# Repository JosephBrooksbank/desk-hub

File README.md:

# desk-hub
A custom KM/USB switch for my desk. 

## Goals
- 10(+) USB Ports
- 2 input switchable
- Stable 5V power to all ports
- Separate overdraw protection
- Electronically controllable
- Visual indicator of port use and overdraw
- Multiple switching points to split input across machines
- USB3?

## Rationale 
Currently, I have two UGreen 4 port USB switches taped to my desk. Each morning I press the button on each to switch to work, and each afternoon I press the button to switch back. They cannot always reliably provide enough amps to each downstream port and my audio cuts out sometimes. Very occasionally they initialize incorrectly and I must remove all connections and reconnect them to gain control again. The downstream and upstream ports are also all on opposite sides, leading to many wires curling back on themselves. 

I aim to solve these issues in an overengineered board of my own design, as an opportunity to learn slightly higher speed PCB design and 4 layer boards.

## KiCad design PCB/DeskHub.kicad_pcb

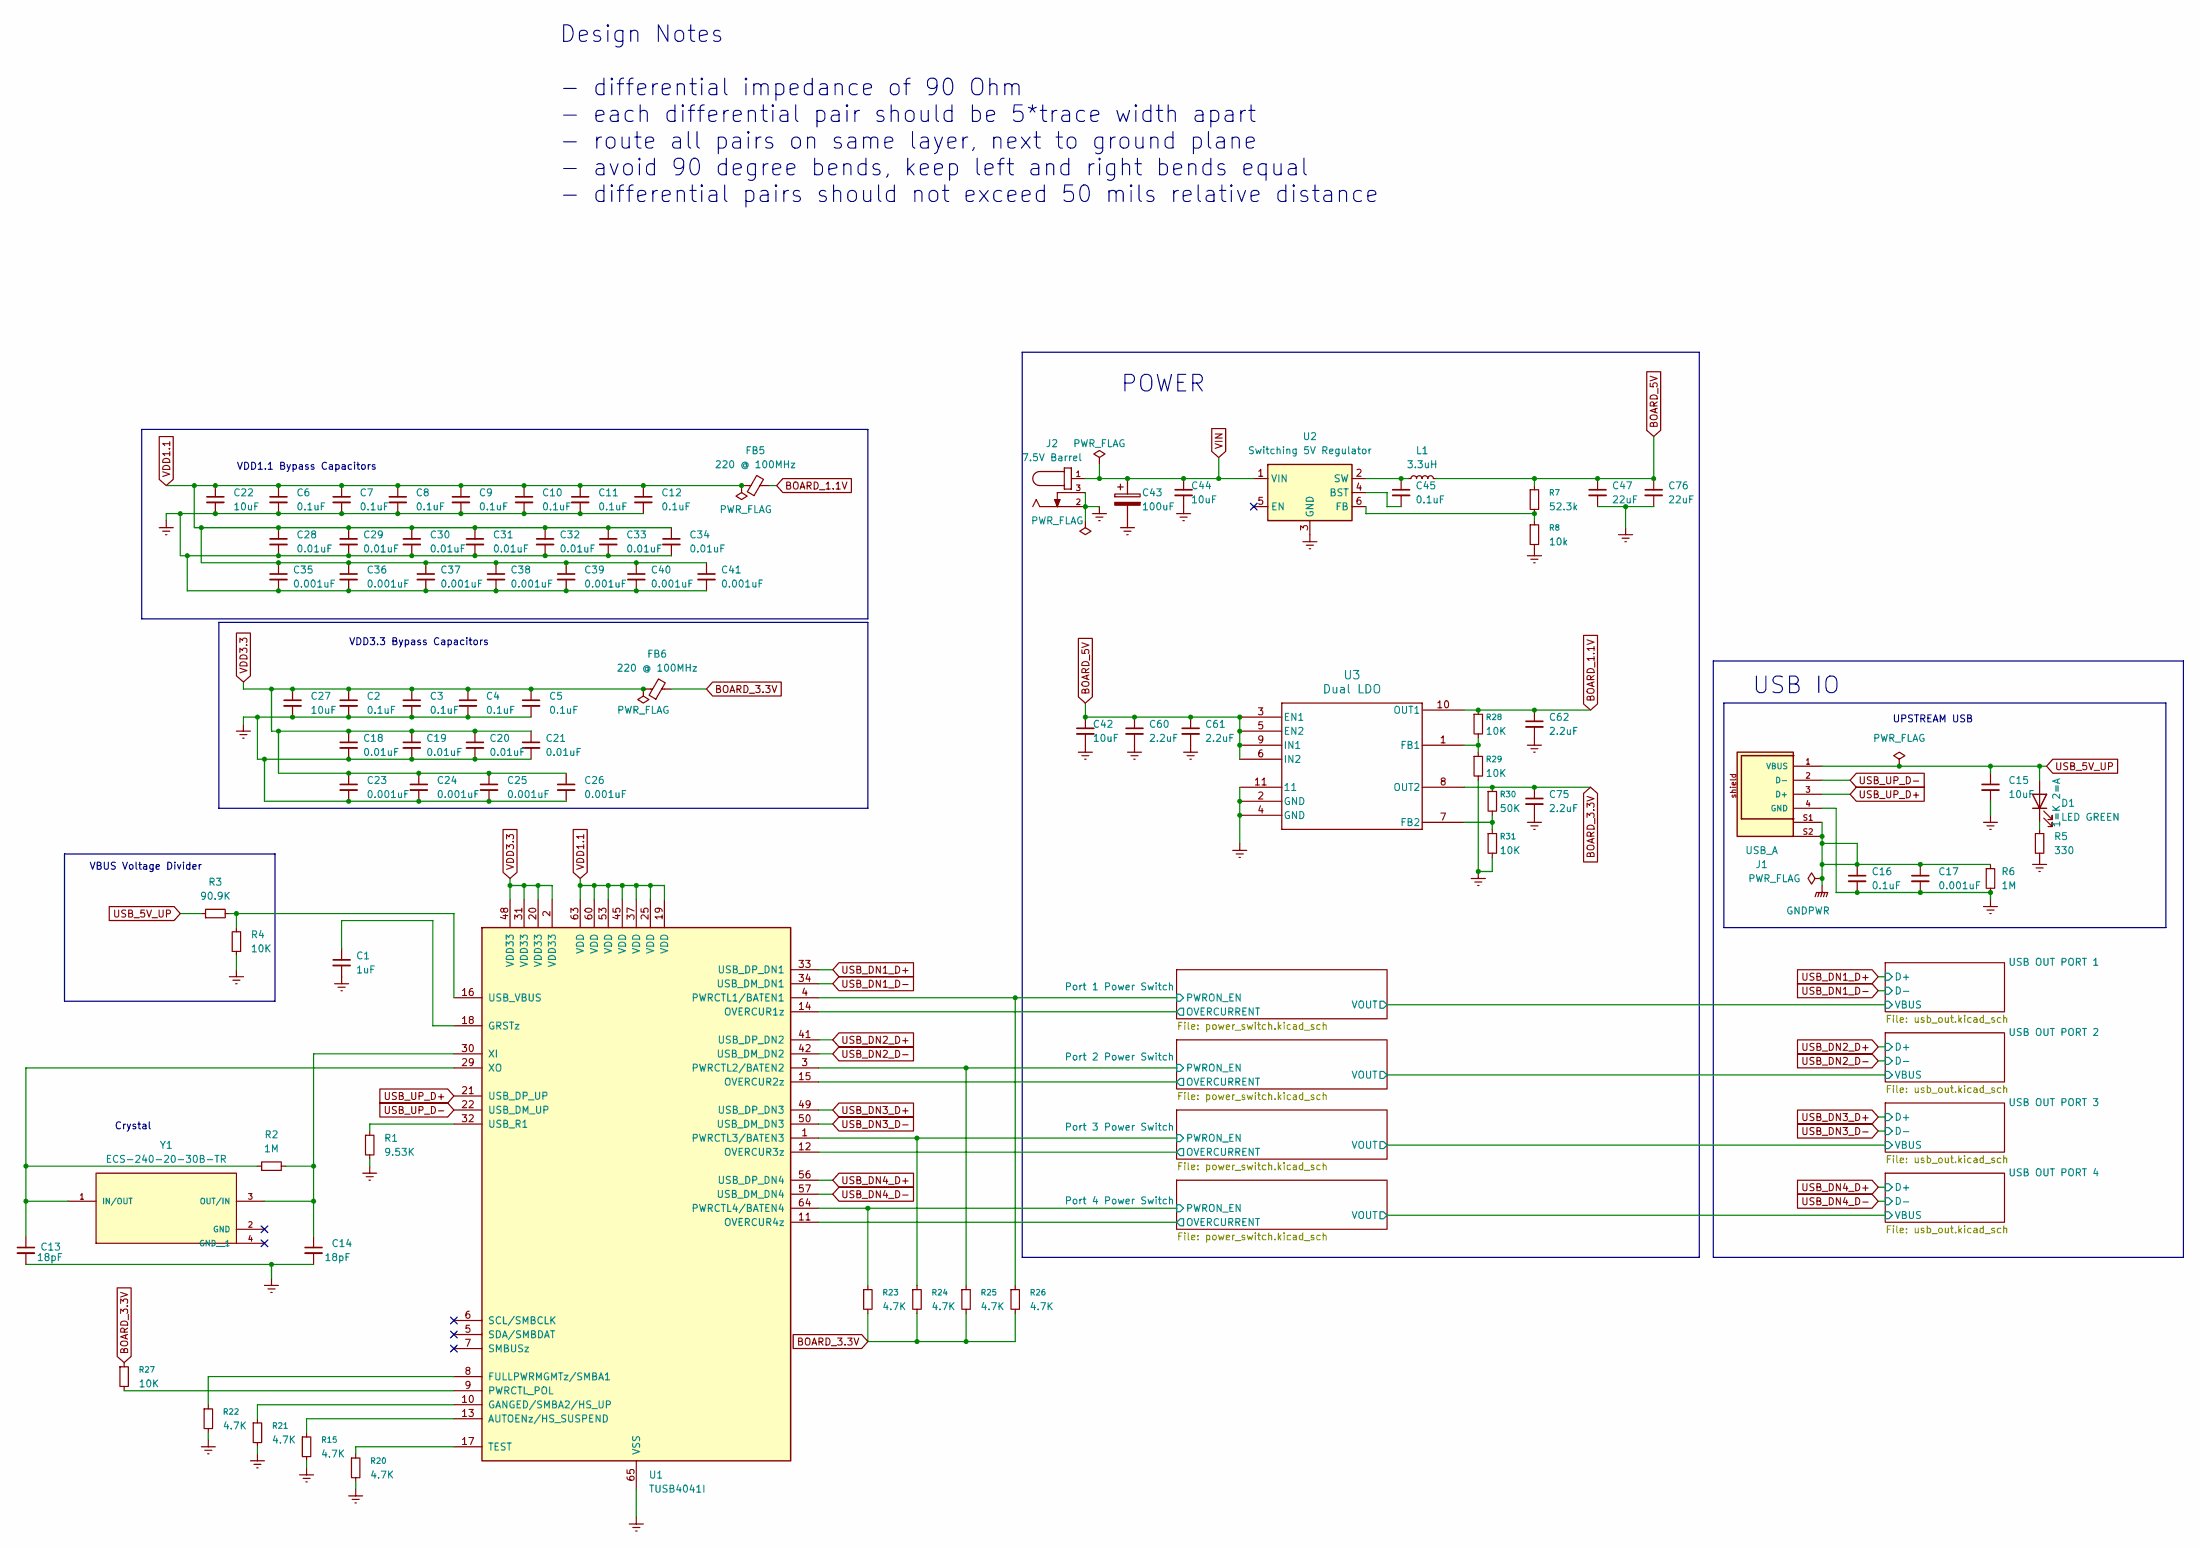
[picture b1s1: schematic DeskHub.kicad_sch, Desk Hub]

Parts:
C1: 1uF; C_0402_1005Metric
C2, C3, C4, C5, C6, C7, C8, C9, C10, C11, C12: 0.1uF; C_0201_0603Metric
C13, C14: 18pF; C_0402_1005Metric
C15, C22, C27, C42, C44: 10uF; C_1206_3216Metric
C16, C45: 0.1uF; C_0402_1005Metric
C17: 0.001uF; C_0402_1005Metric
C18, C19, C20, C21, C28, C29, C30, C31, C32, C33, C34: 0.01uF; C_0201_0603Metric
C23, C24, C25, C26, C35, C36, C37, C38, C39, C40, C41: 0.001uF; C_0201_0603Metric
C43: 100uF; CP_Elec_6.3x7.7
C47, C76: 22uF; C_0201_0603Metric
C60, C61, C62, C75: 2.2uF; C_0805_2012Metric
D1: LED GREEN; LED_0603_1608Metric
FB5, FB6: 220 @ 100MHz; BEADC1608X95N
J1: USB_A; 61400416021
J2: 7.5V Barrel; 694108301002
L1: 3.3uH; NRS5030T3R3MMGJ
R1: 9.53K; R_0402_1005Metric
R2, R6: 1M; R_0402_1005Metric
R3: 90.9K; R_0402_1005Metric
R4, R27, R28, R29, R31: 10K; R_0402_1005Metric
R5: 330; R_0402_1005Metric
R7: 52.3k; R_0402_1005Metric
R8: 10k; R_0402_1005Metric
R15, R20, R21, R22, R23, R24, R25, R26: 4.7K; R_0402_1005Metric
R30: 50K; R_0402_1005Metric
U1: TUSB4041I; HTQFP-64-1EP_10x10mm_P0.5mm_EP8x8mm_Mask4.4x4.4mm_ThermalVi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
U2: Switching 5V Regulator; SOT-563
U3: Dual LDO; SON_1PDSQR_TEX
Y1: ECS-240-20-30B-TR; XTAL_ECS-240-20-30B-TR

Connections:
/Port 1 Power Switch/OVERCURRENT: U1.14 (OVERCUR1z); also elsewhere on the board
/Port 1 Power Switch/PWRON_EN: R26.1, U1.4 (PWRCTL1/BATEN1); also elsewhere on the board
/Port 2 Power Switch/OVERCURRENT: U1.15 (OVERCUR2z); also elsewhere on the board
/Port 2 Power Switch/PWRON_EN: R25.1, U1.3 (PWRCTL2/BATEN2); also elsewhere on the board
/Port 3 Power Switch/OVERCURRENT: U1.12 (OVERCUR3z); also elsewhere on the board
/Port 3 Power Switch/PWRON_EN: R24.1, U1.1 (PWRCTL3/BATEN3); also elsewhere on the board
/Port 4 Power Switch/OVERCURRENT: U1.11 (OVERCUR4z); also elsewhere on the board
/Port 4 Power Switch/PWRON_EN: R23.1, U1.64 (PWRCTL4/BATEN4); also elsewhere on the board
BOARD_1.1V: C62.1, FB5.2, R28.1, U3.10 (OUT1)
BOARD_3.3V: C75.1, FB6.2, R23.2, R24.2, R25.2, R26.2, R27.1, R30.1, U3.8 (OUT2); also elsewhere on the board
BOARD_5V: C42.1, C47.1, C60.1, C61.1, C76.1, L1.2, R7.1, U3.3 (EN1), U3.5 (EN2), U3.6 (IN2), U3.9 (IN1); also elsewhere on the board
Earth: C1.2, C2.2, C3.2, C4.2, C5.2, C6.2, C7.2, C8.2, C9.2, C10.2, C11.2, C12.2, C13.2, C14.2, C15.2, C16.2, C17.2, C18.2, C19.2, C20.2, C21.2, C22.2, C23.2, C24.2, C25.2, C26.2, C27.2, C28.2, C29.2, C30.2, C31.2, C32.2, C33.2, C34.2, C35.2, C36.2, C37.2, C38.2, C39.2, C40.2, C41.2, C42.2, C43.2, C44.2, C47.2, C60.2, C61.2, C62.2, C75.2, C76.2, J1.4 (GND), J2.2, J2.3, R1.2, R4.1, R5.2, R6.2, R8.2, R15.2, R20.2, R21.2, R22.2, R29.2, R31.2, U1.65 (VSS), U2.3 (GND), U3.2 (GND), U3.4 (GND), U3.11; also elsewhere on the board
GNDPWR: C16.1, C17.1, J1.S1, J1.S2, R6.1; also elsewhere on the board
unnamed: D1.1 (K), R5.1
unnamed: R15.1, U1.13 (AUTOENz/HS_SUSPEND)
unnamed: R22.1, U1.8 (FULLPWRMGMTz/SMBA1)
unnamed: R21.1, U1.10 (GANGED/SMBA2/HS_UP)
unnamed: C1.1, U1.18 (GRSTz)
unnamed: R27.2, U1.9 (PWRCTL_POL)
unnamed: R20.1, U1.17 (TEST)
unnamed: R1.1, U1.32 (USB_R1)
unnamed: R3.2, R4.2, U1.16 (USB_VBUS)
unnamed: C14.1, R2.2, U1.30 (XI), Y1.3 (OUT/IN)
unnamed: C13.1, R2.1, U1.29 (XO), Y1.1 (IN/OUT)
unnamed: C45.2, U2.4 (BST)
unnamed: R7.2, R8.1, U2.6 (FB)
unnamed: C45.1, L1.1, U2.2 (SW)
unnamed: R28.2, R29.1, U3.1 (FB1)
unnamed: R30.2, R31.1, U3.7 (FB2)
USB_5V_UP: C15.1, D1.2 (A), J1.1 (VBUS), R3.1
USB_DN1_D+: U1.33 (USB_DP_DN1); also elsewhere on the board
USB_DN1_D-: U1.34 (USB_DM_DN1); also elsewhere on the board
USB_DN2_D+: U1.41 (USB_DP_DN2); also elsewhere on the board
USB_DN2_D-: U1.42 (USB_DM_DN2); also elsewhere on the board
USB_DN3_D+: U1.49 (USB_DP_DN3); also elsewhere on the board
USB_DN3_D-: U1.50 (USB_DM_DN3); also elsewhere on the board
USB_DN4_D+: U1.56 (USB_DP_DN4); also elsewhere on the board
USB_DN4_D-: U1.57 (USB_DM_DN4); also elsewhere on the board
USB_UP_D+: J1.3 (D+), U1.21 (USB_DP_UP)
USB_UP_D-: J1.2 (D-), U1.22 (USB_DM_UP)
VDD1.1: C6.1, C7.1, C8.1, C9.1, C10.1, C11.1, C12.1, C22.1, C28.1, C29.1, C30.1, C31.1, C32.1, C33.1, C34.1, C35.1, C36.1, C37.1, C38.1, C39.1, C40.1, C41.1, FB5.1, U1.19 (VDD), U1.25 (VDD), U1.37 (VDD), U1.45 (VDD), U1.53 (VDD), U1.60 (VDD), U1.63 (VDD)
VDD3.3: C2.1, C3.1, C4.1, C5.1, C18.1, C19.1, C20.1, C21.1, C23.1, C24.1, C25.1, C26.1, C27.1, FB6.1, U1.2 (VDD33), U1.20 (VDD33), U1.31 (VDD33), U1.48 (VDD33)
VIN: C43.1, C44.1, J2.1, U2.1 (VIN)

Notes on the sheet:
UPSTREAM USB
VDD1.1 Bypass Capacitors
Design Notes - differential impedance of 90 Ohm - each differential pair should be 5*trace width apart - route all pairs on same layer, next to ground plane - avoid 90 degree bends, keep left and right bends equal - differential pairs should not exceed 50 mils relative distance
VDD3.3 Bypass Capacitors
USB IO
Crystal
POWER
VBUS Voltage Divider

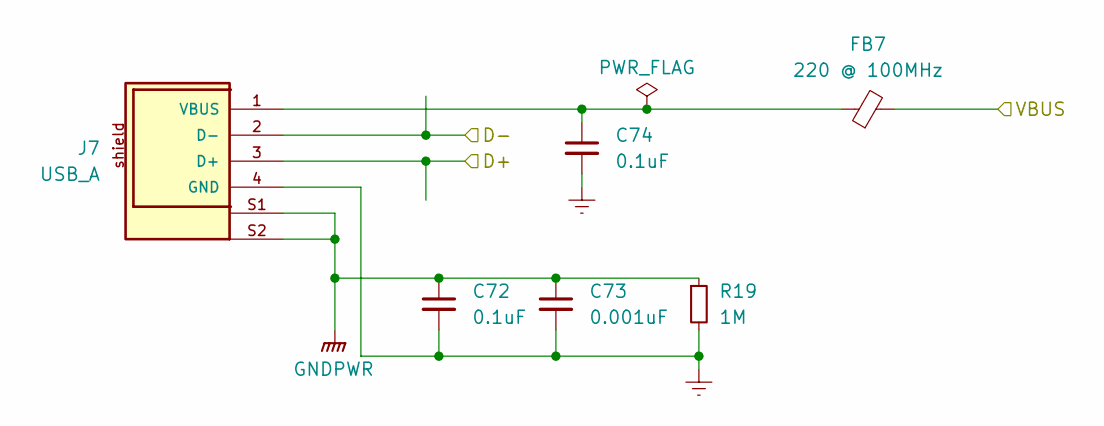
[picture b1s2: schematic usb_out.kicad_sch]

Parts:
C72, C74: 0.1uF; C_0402_1005Metric
C73: 0.001uF; C_0402_1005Metric
FB7: 220 @ 100MHz; BEADC1608X95N
J7: USB_A; 61400416021
R19: 1M; R_0402_1005Metric

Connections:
/Port 1 Power Switch/VOUT: FB7.2; also elsewhere on the board
Earth: C72.2, C73.2, C74.2, J7.4 (GND), R19.2; also elsewhere on the board
GNDPWR: C72.1, C73.1, J7.S1, J7.S2, R19.1; also elsewhere on the board
unnamed: C74.1, FB7.1, J7.1 (VBUS)
USB_DN1_D+: J7.3 (D+); also elsewhere on the board
USB_DN1_D-: J7.2 (D-); also elsewhere on the board

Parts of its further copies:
C63, C65, C66, C68, C69, C71: 0.1uF; C_0402_1005Metric
C64, C67, C70: 0.001uF; C_0402_1005Metric
FB2, FB3, FB4: 220 @ 100MHz; BEADC1608X95N
J4, J5, J6: USB_A; 61400416021
R16, R17, R18: 1M; R_0402_1005Metric

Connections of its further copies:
/Port 2 Power Switch/VOUT: FB2.2; also elsewhere on the board
/Port 3 Power Switch/VOUT: FB3.2; also elsewhere on the board
/Port 4 Power Switch/VOUT: FB4.2; also elsewhere on the board
Earth: C63.2, C64.2, C65.2, C66.2, C67.2, C68.2, C69.2, C70.2, C71.2, J4.4 (GND), J5.4 (GND), J6.4 (GND), R16.2, R17.2, R18.2; also elsewhere on the board
GNDPWR: C63.1, C64.1, C66.1, C67.1, C69.1, C70.1, J4.S1, J4.S2, J5.S1, J5.S2, J6.S1, J6.S2, R16.1, R17.1, R18.1; also elsewhere on the board
unnamed: C65.1, FB2.1, J4.1 (VBUS)
unnamed: C68.1, FB3.1, J5.1 (VBUS)
unnamed: C71.1, FB4.1, J6.1 (VBUS)
USB_DN2_D+: J4.3 (D+); also elsewhere on the board
USB_DN2_D-: J4.2 (D-); also elsewhere on the board
USB_DN3_D+: J5.3 (D+); also elsewhere on the board
USB_DN3_D-: J5.2 (D-); also elsewhere on the board
USB_DN4_D+: J6.3 (D+); also elsewhere on the board
USB_DN4_D-: J6.2 (D-); also elsewhere on the board

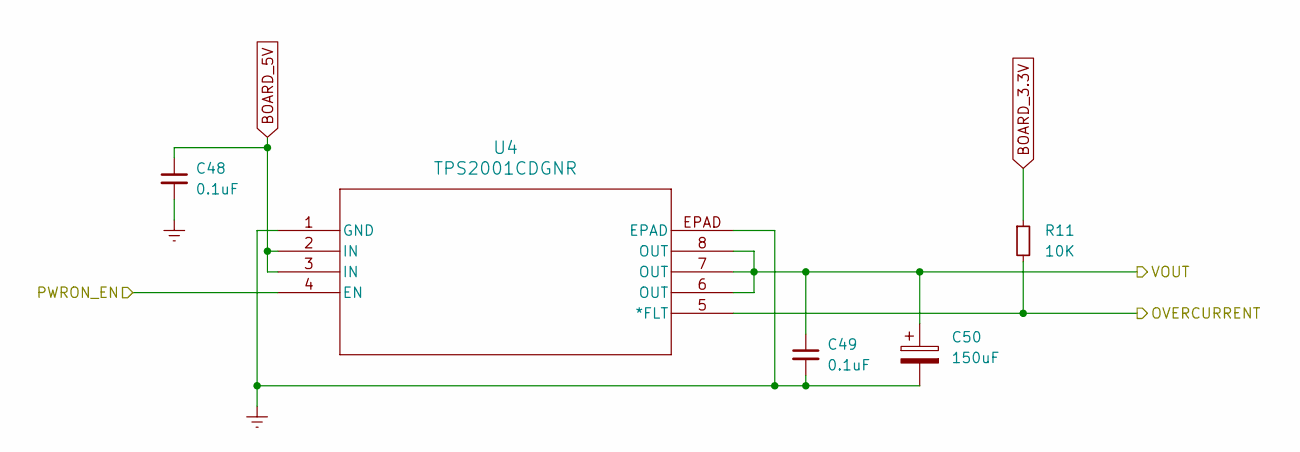
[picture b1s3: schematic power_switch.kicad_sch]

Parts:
C48, C49: 0.1uF; C_0402_1005Metric
C50: 150uF; CAP_EEFCX0J151XR
R11: 10K; R_0402_1005Metric
U4: TPS2001CDGNR; DGN8_1P89X1P57

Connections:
/Port 1 Power Switch/OVERCURRENT: R11.2, U4.5 (*FLT); also elsewhere on the board
/Port 1 Power Switch/PWRON_EN: U4.4 (EN); also elsewhere on the board
/Port 1 Power Switch/VOUT: C49.1, C50.1, U4.6 (OUT), U4.7 (OUT), U4.8 (OUT); also elsewhere on the board
BOARD_3.3V: R11.1; also elsewhere on the board
BOARD_5V: C48.1, U4.2 (IN), U4.3 (IN); also elsewhere on the board
Earth: C48.2, C49.2, C50.2, U4.1 (GND), U4.EPAD; also elsewhere on the board

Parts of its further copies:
C51, C52, C54, C55, C57, C58: 0.1uF; C_0402_1005Metric
C53, C56, C59: 150uF; CAP_EEFCX0J151XR
R12, R13, R14: 10K; R_0402_1005Metric
U5, U6, U7: TPS2001CDGNR; DGN8_1P89X1P57

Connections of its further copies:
/Port 2 Power Switch/OVERCURRENT: R12.2, U5.5 (*FLT); also elsewhere on the board
/Port 2 Power Switch/PWRON_EN: U5.4 (EN); also elsewhere on the board
/Port 2 Power Switch/VOUT: C52.1, C53.1, U5.6 (OUT), U5.7 (OUT), U5.8 (OUT); also elsewhere on the board
/Port 3 Power Switch/OVERCURRENT: R13.2, U6.5 (*FLT); also elsewhere on the board
/Port 3 Power Switch/PWRON_EN: U6.4 (EN); also elsewhere on the board
/Port 3 Power Switch/VOUT: C55.1, C56.1, U6.6 (OUT), U6.7 (OUT), U6.8 (OUT); also elsewhere on the board
/Port 4 Power Switch/OVERCURRENT: R14.2, U7.5 (*FLT); also elsewhere on the board
/Port 4 Power Switch/PWRON_EN: U7.4 (EN); also elsewhere on the board
/Port 4 Power Switch/VOUT: C58.1, C59.1, U7.6 (OUT), U7.7 (OUT), U7.8 (OUT); also elsewhere on the board
BOARD_3.3V: R12.1, R13.1, R14.1; also elsewhere on the board
BOARD_5V: C51.1, C54.1, C57.1, U5.2 (IN), U5.3 (IN), U6.2 (IN), U6.3 (IN), U7.2 (IN), U7.3 (IN); also elsewhere on the board
Earth: C51.2, C52.2, C53.2, C54.2, C55.2, C56.2, C57.2, C58.2, C59.2, U5.1 (GND), U5.EPAD, U6.1 (GND), U6.EPAD, U7.1 (GND), U7.EPAD; also elsewhere on the board

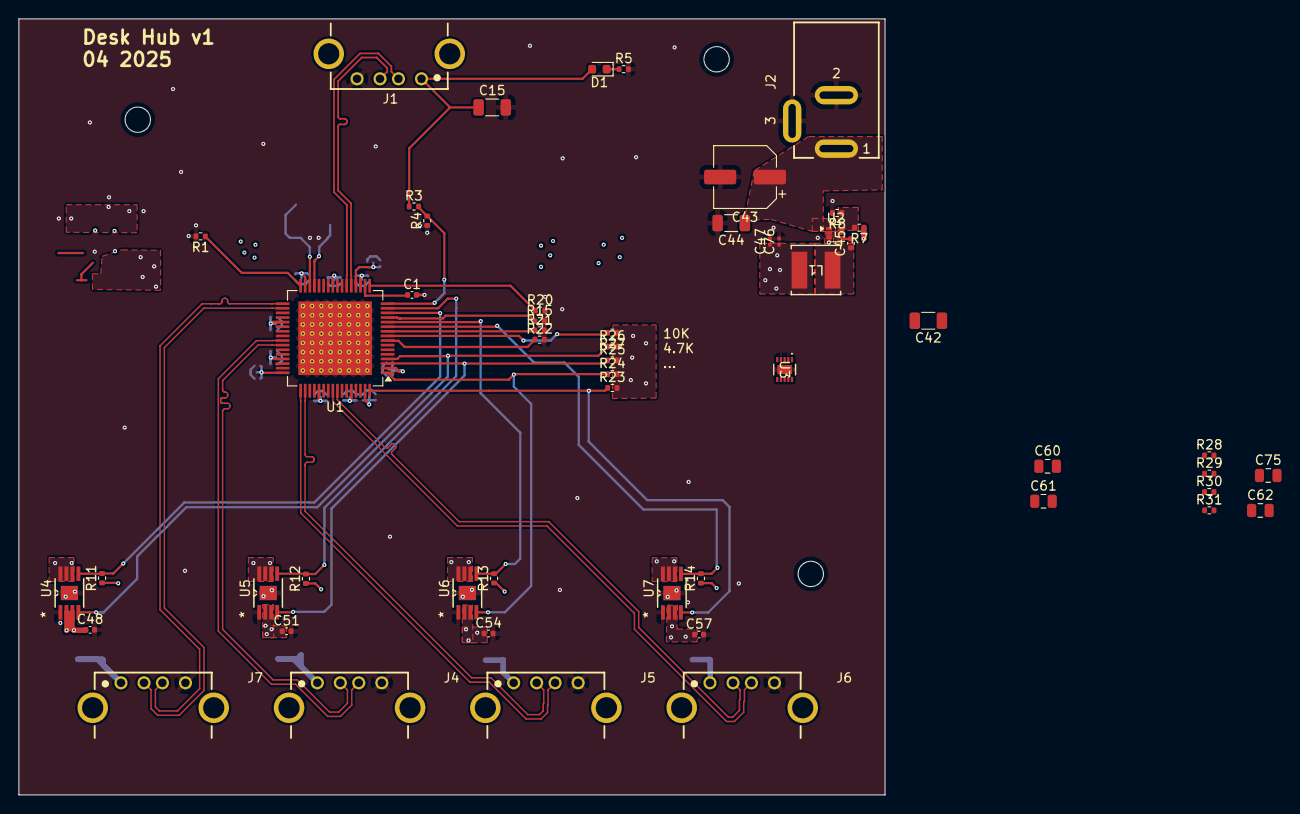
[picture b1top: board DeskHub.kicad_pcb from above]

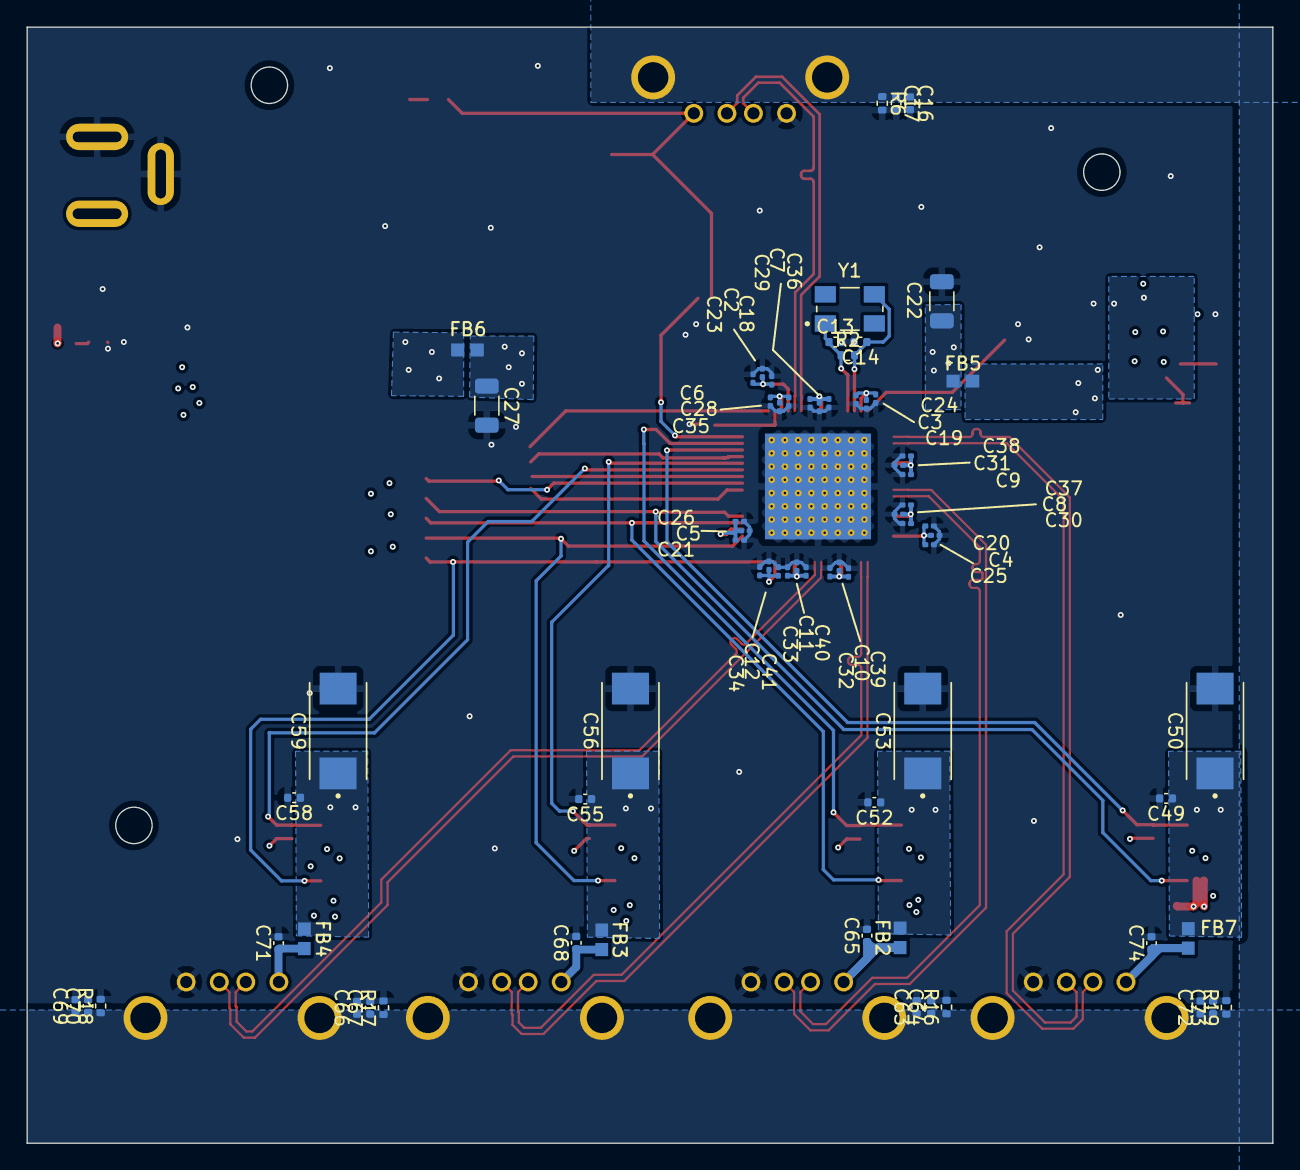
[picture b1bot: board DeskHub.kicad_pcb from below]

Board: 4 copper layers, 94.0 x 84.2 mm, 126 parts (72 on the bottom side), 51 nets.

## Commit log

2025-03-31 Add readme
2025-03-31 comply with ERC
2025-03-31 add net classes
2025-03-31 saved? unsure what
2025-03-31 maybe net classes this time
2025-04-01 Completed schematic!
2025-04-01 adjust schematic to match real components, assign footprints
2025-04-01 begin work on pcb placement... pray for me
2025-04-01 final save of the night
2025-04-02 organized bypass caps into groups
2025-04-02 routed 4041I bypass caps
2025-04-02 saved
2025-04-04 route usb diffs, power for 1 usb partially complete
2025-04-04 cont. work on usb routing
2025-04-04 began power routing
2025-04-07 1.1v power net
2025-04-07 routing done!
2025-04-07 update physical board stats
2025-04-08 finished v1 of board
2025-04-08 Redefine constraints
    using 0.2mm vias doubles the price of the board, so I am going to try
    and not use such small vias.
2025-04-09 pcb v1.1, modified to conform to JLC standards
2025-04-09 pcb v1.2 with JLC mappings
2025-04-09 test
2025-04-09 space out vias, add stiching vias, remove teardrops
2025-04-17 pcb v2.0 condensed
2025-04-17 pcb v2.01 reddit review post
2025-04-25 switching vreg
2025-04-25 add back barrel jack
2025-04-25 add switching power supply
2025-04-28 work on pcb new power
